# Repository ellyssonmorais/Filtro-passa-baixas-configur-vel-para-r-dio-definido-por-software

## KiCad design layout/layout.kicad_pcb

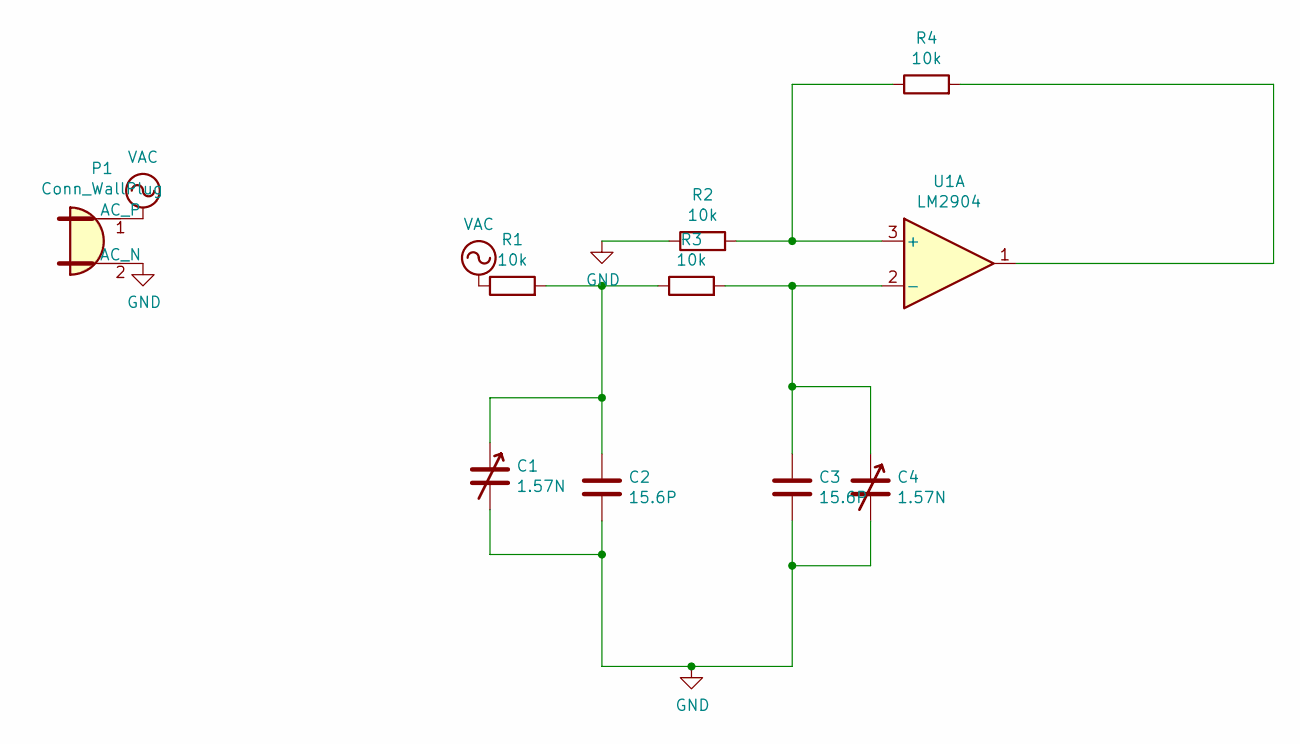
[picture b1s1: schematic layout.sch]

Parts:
C1, C4: 1.57N; C_Trimmer_Murata_TZB4-A
C2, C3: 15.6P; C_0504_1310Metric
P1: Conn_WallPlug
R1, R2, R3, R4: 10k; R_0201_0603Metric
U1: LM2904; SOT-23

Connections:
GND: C1.2, C2.2, C3.2, C4.2, P1.2 (AC_N), R2.1
unnamed: C1.1, C2.1, R1.2, R3.1
unnamed: C3.1, C4.1, R3.2, U1.2 (-)
unnamed: R2.2, R4.1, U1.3 (+)
unnamed: R4.2, U1.1
VAC: P1.1 (AC_P), R1.1

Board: 2 copper layers, 9 parts (0 on the bottom side), 5 nets, no tracks yet.

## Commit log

2020-12-09 arquivo multisim
2020-12-13 projeto atualizado multisim
2020-12-13 arquivos do layout
2020-12-13 arquivos do relatório e lista de compras
2020-12-13 vídeo com comentários sobre o projeto
